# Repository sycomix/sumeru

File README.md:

# sumeru
  An open-source RISC-V CPU core and hardware platform for Altera Cyclone-IV FPGAs.

## Coremark Performance

### Summary

Sumeru @ 75 MHz - 3 stage pipeline - 4K ICACHE 4K DCACHE - MEM STACK

Compiler Flag | Binary Size | Result
------------- | ----------- | ------
-Os | 11784 | 100
-O | 13008 | 105
-O2 | 13092 | 133
-O3 | 16280 | 143

** MEM MALLOC and MEM STATIC performance is similar

### Detail

```
2K performance run parameters for coremark.
CoreMark Size    : 666
Total ticks      : 1165127873
Total time (secs): 15
Iterations/Sec   : 133
Iterations       : 2000
Compiler version : 9.2.0
Compiler flags   : -O2
Memory location  : STACK
seedcrc          : 0xe9f5
[0]crclist       : 0xe714
[0]crcmatrix     : 0x1fd7
[0]crcstate      : 0x8e3a
[0]crcfinal      : 0x4983
Correct operation validated. See README.md for run and reporting rules.

2K performance run parameters for coremark.
CoreMark Size    : 666
Total ticks      : 1165095923
Total time (secs): 15
Iterations/Sec   : 133
Iterations       : 2000
Compiler version : 9.2.0
Compiler flags   : -O2
Memory location  : BSS
seedcrc          : 0xe9f5
[0]crclist       : 0xe714
[0]crcmatrix     : 0x1fd7
[0]crcstate      : 0x8e3a
[0]crcfinal      : 0x4983
Correct operation validated. See README.md for run and reporting rules.

2K performance run parameters for coremark.
CoreMark Size    : 666
Total ticks      : 1165033531
Total time (secs): 15
Iterations/Sec   : 133
Iterations       : 2000
Compiler version : 9.2.0
Compiler flags   : -O2
Memory location  : HEAP
seedcrc          : 0xe9f5
[0]crclist       : 0xe714
[0]crcmatrix     : 0x1fd7
[0]crcstate      : 0x8e3a
[0]crcfinal      : 0x4983
Correct operation validated. See README.md for run and reporting rules.
```

## Commercial soft-core performance 

*Sumeru @ 75 MHz - 3 stage pipeline - 4K ICACHE 4K DCACHE - MEM STACK - Cyclone IV = 143 Coremark*

* [Altera NIOS II CycloneIII](https://www.eembc.org/coremark/view.php?benchmark_seq=1535)
* [Altera Nios II - 80 MHz (apple2apple 119 Coremark)](https://www.eembc.org/coremark/view.php?benchmark_seq=1336)
* [Altera Nios II - 200 MHz](https://www.eembc.org/coremark/view.php?benchmark_seq=1486)
* [Altera Nios II - 200 MHz](https://www.eembc.org/coremark/view.php?benchmark_seq=1487)
* [Altera Nios II/f - 100 MHz](https://www.eembc.org/coremark/view.php?benchmark_seq=2483)

* [Xilinx MicroBlaze v7.20.d in Spartan XC3S700A FPGA, 3-stage pipeline, 2K/2K cache](https://www.eembc.org/coremark/view.php?benchmark_seq=1042)
* [Xilinx MicroBlaze v7.20.d in Spartan XC3S700A FPGA, 5-stage pipeline, 4K/4K cache, integer divider, barrel shifter - 62.5 MHz (apple2apple 103 Coremark)](https://www.eembc.org/coremark/view.php?benchmark_seq=1043)
* [Xilinx MicroBlaze 7.10d in Virtex4-FX20 FPGA, 5-stage pipeline, 16K/16K cache](https://www.eembc.org/coremark/view.php?benchmark_seq=1287)
* [Xilinx MicroBlaze v8.20.b in Virtex5 FPGA, 5-stage pipeline, 16K/16K cache](https://www.eembc.org/coremark/view.php?benchmark_seq=1345)

[Coremark Results Website](https://www.eembc.org/coremark/scores.php)

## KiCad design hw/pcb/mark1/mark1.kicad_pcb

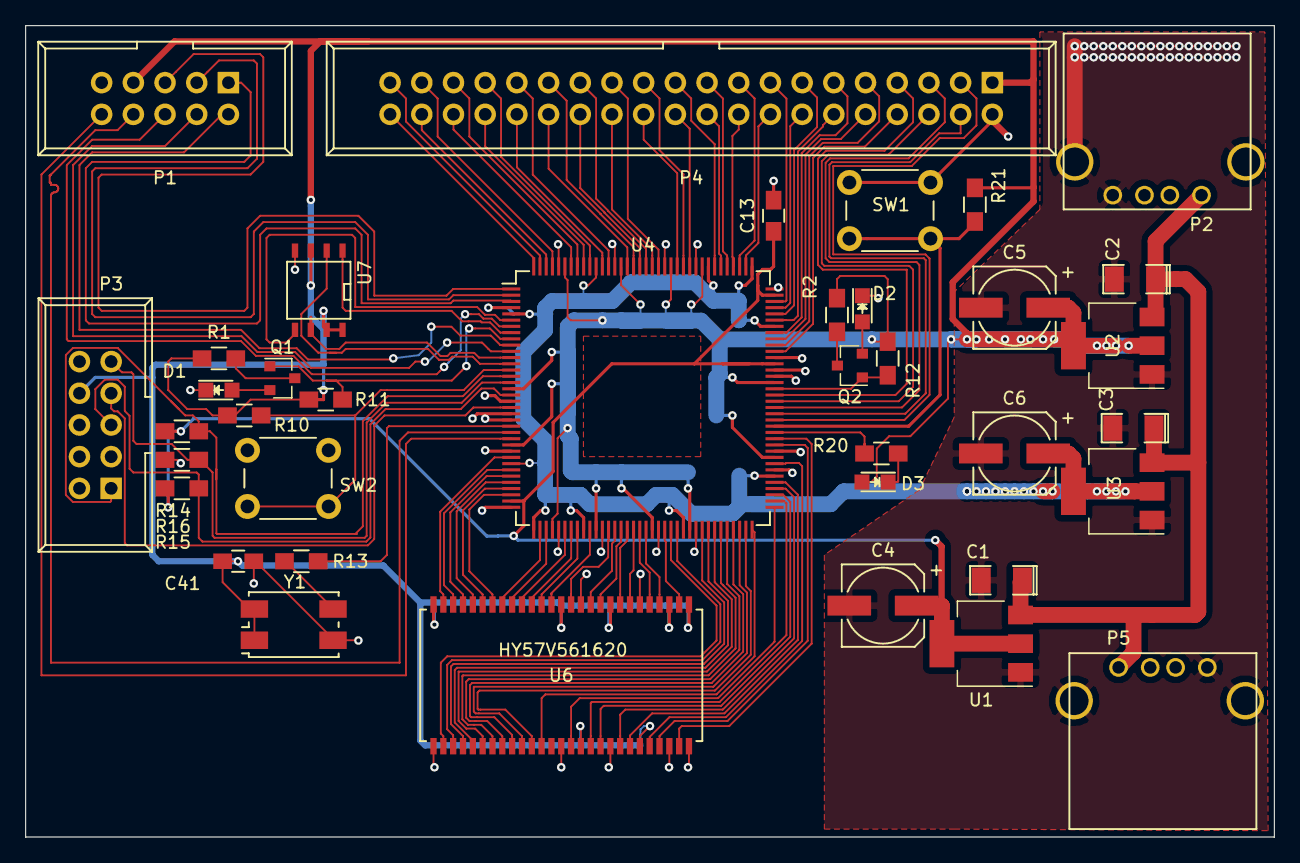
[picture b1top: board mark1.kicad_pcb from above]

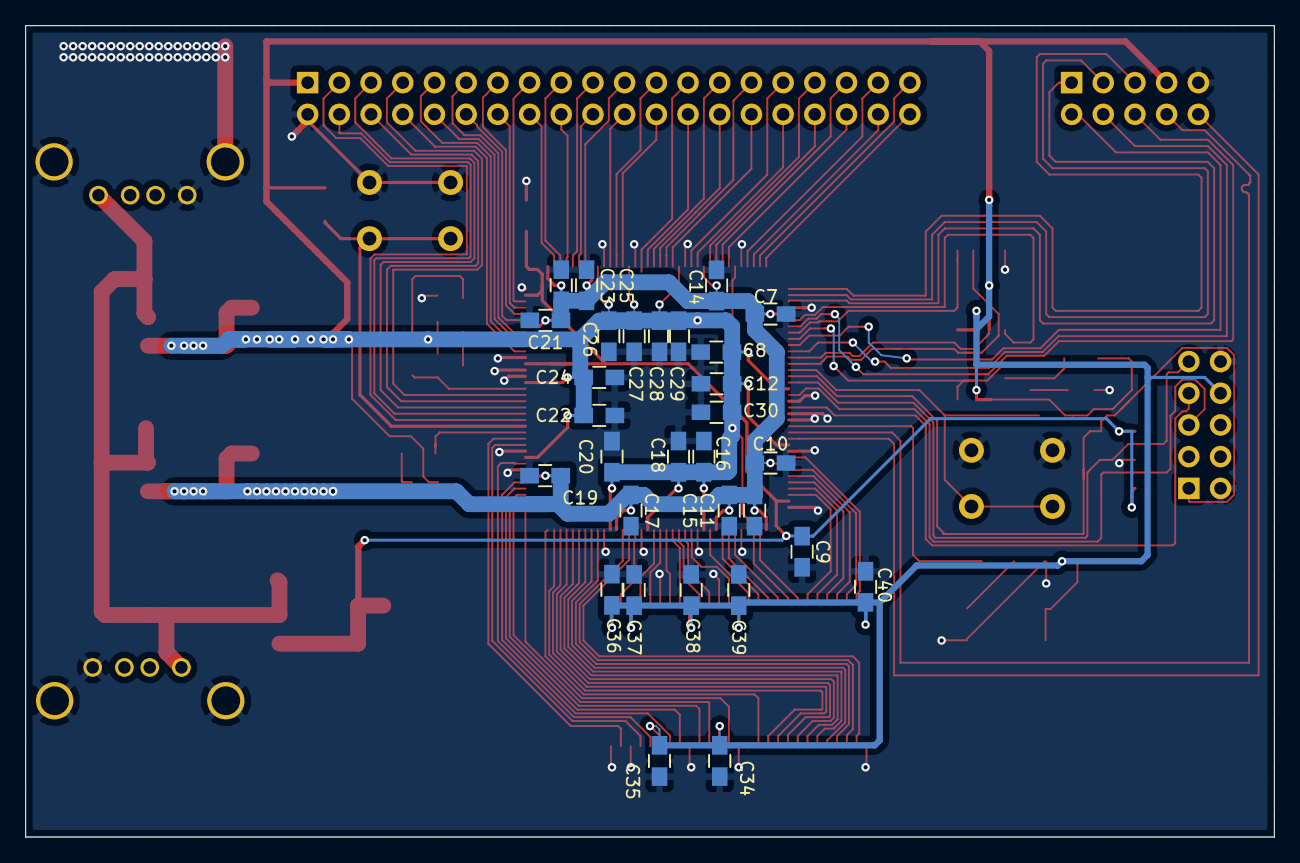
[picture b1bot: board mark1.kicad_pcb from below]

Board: 2 copper layers, 100.1 x 65.0 mm, 68 parts (30 on the bottom side), 110 nets.

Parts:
C1, C2, C3: 10uF; SMD-1206_Pol
C4, C5, C6: 100uF; c_elec_6.3x7.7
C7, C8, C9, C10, C11, C12, C13, C14, C15, C16, C17, C18, C19, C20, C21, C22, C23, C24, C25, C26, C27, C28, C29, C30, C34, C35, C36, C37, C38, C39, C40, C41: 100nF; C_0805_HandSoldering
D1, D2, D3: LED; LED_0805
P1, P3: CONN_02X05; IDC_Header_Straight_10pins
P2, P5: USB_A
P4: CONN_02X20; IDC_Header_Straight_40pins
Q1, Q2: MMBT3904; SOT-23
R1, R2, R16, R20: 1K; R_0805_HandSoldering
R10, R11, R12, R14, R15: 10K; R_0805_HandSoldering
R13: 33; R_0805_HandSoldering
R21: 1k; R_0805_HandSoldering
SW1, SW2: SW_Push; SW_PUSH_6mm_h4.3mm
U1: AMS1117-2.5; SOT-223
U2: AMS1117-3.3; SOT-223
U3: AMS1117-1.2; SOT-223
U4: EP4CE10E22C8N; TQFP-144_20x20mm_Pitch0.5mm
U6: HY57V561620; WIN_TSOP-54
U7: W25Q32FVSSIQ; SOIC-8-N
Y1: Crystal_GND23; Crystal_SMD_7050_4Pads_R

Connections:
/FPGA Configuration Circuitry/FLASH_MISO: U4.13, U7.2
/FPGA Configuration Circuitry/FLASH_MOSI: U4.6, U7.5
/FPGA Configuration Circuitry/FLASH_SCK: U4.12, U7.6
/FPGA Configuration Circuitry/FLASH_nCE: U4.8, U7.1
/FPGA Configuration Circuitry/F_CLK1: R13.2, U4.23
/FPGA Configuration Circuitry/JTAG_TCK: P3.9, R16.2, U4.16
/FPGA Configuration Circuitry/JTAG_TDI: P3.1, R14.2, U4.15
/FPGA Configuration Circuitry/JTAG_TDO: P3.7, U4.20
/FPGA Configuration Circuitry/JTAG_TMS: P3.5, R15.2, U4.18
/FPGA IO Circuitry/SDRAM1: U4.28, U6.26
/FPGA IO Circuitry/SDRAM2: U4.30, U6.25
/FPGA IO Circuitry/SDRAM3: U4.31, U6.24
/FPGA IO Circuitry/SDRAM4: U4.32, U6.23
/FPGA IO Circuitry/SDRAM5: U4.33, U6.22
/FPGA IO Circuitry/SDRAM6: U4.34, U6.21
/FPGA IO Circuitry/SDRAM7: U4.38, U6.20
/FPGA IO Circuitry/SDRAM8: U4.39, U6.19
/FPGA IO Circuitry/SDRAM9: U4.42, U6.18
/FPGA IO Circuitry/SDRAM10: U4.43, U6.17
/FPGA IO Circuitry/SDRAM11: U4.44, U6.16
/FPGA IO Circuitry/SDRAM12: U4.46, U6.15
/FPGA IO Circuitry/SDRAM13: U4.49, U6.13
/FPGA IO Circuitry/SDRAM14: U4.50, U6.11
/FPGA IO Circuitry/SDRAM15: U4.51, U6.10
/FPGA IO Circuitry/SDRAM16: U4.52, U6.8
/FPGA IO Circuitry/SDRAM17: U4.53, U6.7
/FPGA IO Circuitry/SDRAM18: U4.54, U6.5
/FPGA IO Circuitry/SDRAM19: U4.55, U6.4
/FPGA IO Circuitry/SDRAM20: U4.58, U6.2
/FPGA IO Circuitry/SDRAM21: U4.59, U6.29
/FPGA IO Circuitry/SDRAM22: U4.60, U6.30
/FPGA IO Circuitry/SDRAM23: U4.64, U6.31
/FPGA IO Circuitry/SDRAM24: U4.65, U6.32
/FPGA IO Circuitry/SDRAM25: U4.66, U6.33
/FPGA IO Circuitry/SDRAM26: U4.67, U6.34
/FPGA IO Circuitry/SDRAM27: U4.68, U6.35
/FPGA IO Circuitry/SDRAM28: U4.69, U6.36
/FPGA IO Circuitry/SDRAM29: U4.70, U6.37
/FPGA IO Circuitry/SDRAM30: U4.71, U6.38
/FPGA IO Circuitry/SDRAM31: U4.72, U6.39
/FPGA IO Circuitry/SDRAM32: U4.73, U6.42
/FPGA IO Circuitry/SDRAM33: U4.74, U6.44
/FPGA IO Circuitry/SDRAM34: U4.75, U6.45
/FPGA IO Circuitry/SDRAM35: U4.76, U6.47
/FPGA IO Circuitry/SDRAM36: U4.77, U6.48
/FPGA IO Circuitry/SDRAM37: U4.80, U6.50
/FPGA IO Circuitry/SDRAM38: U4.83, U6.51
/FPGA IO Circuitry/SDRAM39: U4.84, U6.53
F_CLK2: P1.8, U4.24
F_CLK3: P1.10, U4.25
F_CLK4: P4.7, U4.91
F_CLK5: P4.6, U4.90
F_CLK6: P4.5, U4.89
F_CLK7: P4.4, U4.88
GND: C1.2, C2.2, C3.2, C4.2, C5.2, C6.2, C7.2, C8.2, C9.2, C10.2, C11.2, C12.2, C13.2, C14.2, C15.2, C16.2, C17.2, C18.2, C19.2, C20.2, C21.2, C22.2, C23.2, C24.2, C25.2, C26.2, C27.2, C28.2, C29.2, C30.2, C34.2, C35.2, C36.2, C37.2, C38.2, C39.2, C40.2, C41.1, D1.1, D2.1, P1.9, P2.4, P2.5, P3.2, P3.10, P4.2, P5.4, P5.5, R16.1, SW1.1, SW2.1, U1.1, U2.1, U3.1, U4.4, U4.19, U4.21, U4.22, U4.27, U4.36, U4.41, U4.48, U4.57, U4.63, U4.79, U4.82, U4.94, U4.95, U4.97, U4.108, U4.118, U4.123, U4.131, U4.140, U6.6, U6.12, U6.28, U6.41, U6.46, U6.52, U6.54, U7.4, Y1.2
unnamed: D1.2, Q1.2
unnamed: D2.2, Q2.2
unnamed: D3.1, R20.2
unnamed: P1.1, U4.3
unnamed: P1.2, U4.10
unnamed: P1.3, U4.2
unnamed: P1.4, U4.11
unnamed: P1.5, U4.1
unnamed: P1.6, U4.7
unnamed: Q1.1, R11.1, U4.9
unnamed: Q1.3, R1.2
unnamed: Q2.1, R12.1, U4.92
unnamed: Q2.3, R2.2
unnamed: R10.1, SW2.2, U4.14
unnamed: R13.1, Y1.3
unnamed: R21.1, SW1.2, U4.86
PIN85: R20.1, U4.85
PIN87: P4.3, U4.87
PIN98: P4.8, U4.98
PIN99: P4.9, U4.99
PIN100: P4.10, U4.100
PIN101: P4.11, U4.101
PIN103: P4.12, U4.103
PIN104: P4.13, U4.104
PIN105: P4.14, U4.105
PIN106: P4.15, U4.106
PIN110: P4.16, U4.110
PIN111: P4.17, U4.111
PIN112: P4.18, U4.112
PIN113: P4.19, U4.113
PIN114: P4.20, U4.114
PIN115: P4.21, U4.115
PIN119: P4.22, U4.119
PIN120: P4.23, U4.120
PIN121: P4.24, U4.121
PIN124: P4.25, U4.124
PIN125: P4.26, U4.125
PIN126: P4.27, U4.126
PIN127: P4.28, U4.127
PIN128: P4.29, U4.128
PIN129: P4.30, U4.129
PIN132: P4.31, U4.132
PIN133: P4.32, U4.133
PIN135: P4.33, U4.135
PIN136: P4.34, U4.136
PIN137: P4.35, U4.137
PIN138: P4.36, U4.138
PIN141: P4.37, U4.141
PIN142: P4.38, U4.142
PIN143: P4.39, U4.143
PIN144: P4.40, U4.144
VCC: C1.1, C2.1, C3.1, P2.1, P5.1, U1.3, U2.3, U3.3
VCC1p2: C6.1, C7.1, C10.1, C11.1, C14.1, C15.1, C17.1, C19.1, C21.1, C23.1, C25.1, U3.2, U3.4, U4.5, U4.29, U4.37, U4.45, U4.61, U4.78, U4.102, U4.109, U4.116, U4.134
VCC2p5: C4.1, C9.1, C13.1, R14.1, R15.1, U1.2, U1.4, U4.35, U4.96, U4.107
VCC3p3: C5.1, C8.1, C12.1, C16.1, C18.1, C20.1, C22.1, C24.1, C26.1, C27.1, C28.1, C29.1, C30.1, C34.1, C35.1, C36.1, C37.1, C38.1, C39.1, C40.1, C41.2, D3.2, P1.7, P3.8, P4.1, R1.1, R2.1, R10.2, R11.2, R12.2, R21.2, U2.2, U2.4, U4.17, U4.26, U4.40, U4.47, U4.56, U4.62, U4.81, U4.93, U4.117, U4.122, U4.130, U4.139, U6.1, U6.3, U6.9, U6.14, U6.27, U6.43, U6.49, U7.3, U7.7, U7.8, Y1.1, Y1.4

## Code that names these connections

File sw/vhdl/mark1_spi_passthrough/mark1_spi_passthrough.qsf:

# -------------------------------------------------------------------------- #
#
# Copyright (C) 1991-2014 Altera Corporation. All rights reserved.
# Your use of Altera Corporation's design tools, logic functions 
# and other software and tools, and its AMPP partner logic 
# functions, and any output files from any of the foregoing 
# (including device programming or simulation files), and any 
# associated documentation or information are expressly subject 
# to the terms and conditions of the Altera Program License 
# Subscription Agreement, the Altera Quartus II License Agreement,
# the Altera MegaCore Function License Agreement, or other 
# applicable license agreement, including, without limitation, 
# that your use is for the sole purpose of programming logic 
# devices manufactured by Altera and sold by Altera or its 
# authorized distributors.  Please refer to the applicable 
# agreement for further details.
#
# -------------------------------------------------------------------------- #
#
# Quartus II 64-Bit
# Version 14.1.0 Build 186 12/03/2014 Patches 0.19 SJ Web Edition
# Date created = 13:06:18  July 10, 2018
#
# -------------------------------------------------------------------------- #
#
# Notes:
#
# 1) The default values for assignments are stored in the file:
#		toplevel_assignment_defaults.qdf
#    If this file doesn't exist, see file:
#		assignment_defaults.qdf
#
# 2) Altera recommends that you do not modify this file. This
#    file is updated automatically by the Quartus II software
#    and any changes you make may be lost or overwritten.
#
# -------------------------------------------------------------------------- #


set_global_assignment -name FAMILY "Cyclone IV E"
set_global_assignment -name DEVICE EP4CE10E22C8
set_global_assignment -name TOP_LEVEL_ENTITY mark1_spi_passthrough
set_global_assignment -name ORIGINAL_QUARTUS_VERSION "14.1.0 SP0.19"
set_global_assignment -name PROJECT_CREATION_TIME_DATE "13:06:18  JULY 10, 2018"
set_global_assignment -name LAST_QUARTUS_VERSION "19.1.0 Lite Edition"
set_global_assignment -name PROJECT_OUTPUT_DIRECTORY output_files
set_global_assignment -name MIN_CORE_JUNCTION_TEMP 0
set_global_assignment -name MAX_CORE_JUNCTION_TEMP 85
set_global_assignment -name DEVICE_FILTER_PACKAGE TQFP
set_global_assignment -name ERROR_CHECK_FREQUENCY_DIVISOR 1
set_global_assignment -name DEVICE_FILTER_PIN_COUNT 144
set_global_assignment -name DEVICE_FILTER_SPEED_GRADE 8
set_global_assignment -name PARTITION_NETLIST_TYPE SOURCE -section_id Top
set_global_assignment -name PARTITION_FITTER_PRESERVATION_LEVEL PLACEMENT_AND_ROUTING -section_id Top
set_global_assignment -name PARTITION_COLOR 16764057 -section_id Top
set_global_assignment -name STRATIX_DEVICE_IO_STANDARD "3.3-V LVTTL"
set_location_assignment PIN_23 -to clk_50m
set_location_assignment PIN_85 -to led
set_global_assignment -name POWER_PRESET_COOLING_SOLUTION "23 MM HEAT SINK WITH 200 LFPM AIRFLOW"
set_global_assignment -name POWER_BOARD_THERMAL_MODEL "NONE (CONSERVATIVE)"
set_global_assignment -name VHDL_FILE mark1_spi_passthrough.vhd
set_global_assignment -name VHDL_FILE pll.vhd
set_global_assignment -name ENABLE_OCT_DONE OFF
set_global_assignment -name ENABLE_CONFIGURATION_PINS OFF
set_global_assignment -name ENABLE_BOOT_SEL_PIN OFF
set_global_assignment -name USE_CONFIGURATION_DEVICE OFF
set_global_assignment -name CRC_ERROR_OPEN_DRAIN OFF
set_global_assignment -name OUTPUT_IO_TIMING_NEAR_END_VMEAS "HALF VCCIO" -rise
set_global_assignment -name OUTPUT_IO_TIMING_NEAR_END_VMEAS "HALF VCCIO" -fall
set_global_assignment -name OUTPUT_IO_TIMING_FAR_END_VMEAS "HALF SIGNAL SWING" -rise
set_global_assignment -name OUTPUT_IO_TIMING_FAR_END_VMEAS "HALF SIGNAL SWING" -fall
set_global_assignment -name RESERVE_ALL_UNUSED_PINS_WEAK_PULLUP "AS INPUT TRI-STATED"
set_global_assignment -name RESERVE_DATA0_AFTER_CONFIGURATION "USE AS REGULAR IO"
set_global_assignment -name RESERVE_DATA1_AFTER_CONFIGURATION "USE AS REGULAR IO"
set_global_assignment -name RESERVE_FLASH_NCE_AFTER_CONFIGURATION "USE AS REGULAR IO"
set_global_assignment -name RESERVE_DCLK_AFTER_CONFIGURATION "USE AS REGULAR IO"
set_global_assignment -name CYCLONEII_RESERVE_NCEO_AFTER_CONFIGURATION "USE AS PROGRAMMING PIN"
set_location_assignment PIN_13 -to flash_miso
set_location_assignment PIN_6 -to flash_mosi
set_location_assignment PIN_12 -to flash_sck
set_location_assignment PIN_8 -to flash_nce
set_location_assignment PIN_11 -to mosi
set_location_assignment PIN_7 -to miso
set_location_assignment PIN_24 -to sck
set_location_assignment PIN_10 -to nce


set_instance_assignment -name PARTITION_HIERARCHY root_partition -to | -section_id Top

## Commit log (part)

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2019-12-24 Branch working
2019-12-25 ERRATICALLY BUGGY VERSION: WIP
2019-12-26 JALR (trigger_cxfer) working
2019-12-26 WIP: Load byteena and correctly sized & signed output implemented
2019-12-26 FENCE.I is working
2019-12-26 Implement DCACHE LINE FLUSH by extending the STORE INSTRUCTION - funct3 = 011 or 111
2019-12-26 DCACHE FLUSH Example in BOOTCODE.s
2019-12-27 NEW CSR bus implementation
2019-12-27 WIP: C based boot code
2019-12-28 Bugfix: STORE immediate
2019-12-28 MULTIPLY implemented
2019-12-29 Multiply working, use regfile_wren to detect valid last writte values in iexec
2019-12-30 DIVIDE working: 4 stage pipeline - 5 cycle counter delay in iexec
2019-12-30 Adjust env.sh makefiles to avoid setting MAKEFILES in env.sh -- set in Makefile instead
2019-12-30 Rehaul BOOTCODE code build strategy, IVECTOR WIP
2019-12-30 Disable -gc-sections MK_LDFLAGS
2019-12-31 Add gtkw to examples
2019-12-31 DIVEIDE Bugfix: Increase div_ctr to 6 (was 5)
2019-12-31 INTERRUPTS WIP
2020-01-01 CSR Renumbering
2020-01-01 Add intr_controller.vhd
2020-01-01 BUGFIX: Interrupt Handling in idecode
2020-01-01 **RADICAL changes to ifetch and idecode to facilitate raising of interrupts. c6ab235fc192d14625a0c713357f9949c8f2c8c9 is a know good state before these changes
2020-01-02 CSR sel bit delay introduced, INTR RETURN WIP
2020-01-03 CPU IDECODE Overhauld / Rewrite
2020-01-03 CPU IDECODE Overhaul / Rewrite: WIP
2020-01-03 GOOD VERSION: INTR RETURN WORKING. Bug: Don't set cxfer on OP_TYPE_B in decode. Bug: Output complete address from interrupt handler instead of a partial vector; Partial vector with concatenation does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
2020-01-04 Revert last changes to CSR numbering
2020-01-04 Buggy Version. Seem like previous fix to intr_handler to emit full address still does not work. This version shows different behaviour for simulation and actual. Seems like immediate is not getting c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
2020-01-04 Rearrange assignment for iexec_in.imm <= ctx_pc_switch
2020-01-04 IRET (aka. switch) seems to be working -- more testing needed
2020-01-05 WIP: Getting Ready to RUN riscv-tests
2020-01-05 Add riscv-test to REPO
2020-01-05 Adjust riscv-tests for SAKE
2020-01-05 Makefile changed to run risc-test via BC_FILE variable
2020-01-05 SHIFT BUGFIX - srai sign bit fix
2020-01-05 riscv-test env add support for test data
2020-01-05 ***GOOD VERSION: All riscv rv32i tests except fence.i, mul and div are tested working
2020-01-05 Bug fix: mulh was being decoded as shift -- mulh working
2020-01-05 DIV(U) and REM(U) working with minimal latency (emphirically checked @85MHZ) of pipeline 8 and counter 9 -- counter 8 does not work nor does pipeline 6
2020-01-05 Modify riscv-test fence test to perform a D-Cache line flush prior to initiating the fence.i instruction
2020-01-05 **GOOD VERSION: All riscv rv32imu tests pass with this version -- time to reintegrate back from REWORK into cpu_v2 master
2020-01-06 Reintroduce intr_controller, csr_timer, csr_counters. Renumber CSR Registers to coform to RV spec
2020-01-06 ***GOOD VERSION: RV32IMU-tested+intr: INTR RET is working
2020-01-06 Minimum delay requied between writing to CSR_REG_PC_SWITCH and CSR_REG_SWITCH is 2 NOPS
2020-01-06 Add support for interrupt reset
2020-01-06 INTR ret wip
2020-01-06 cometic change reverted idecode
2020-01-06 **GOOD VERSION: INTERRUPT HANDLING IS DONE : Invariant If device intr-ack csr is written just before csr_switch is written the device intr-line is being lowered in time to avoid errors.
2020-01-06 REWORK : CPU_V2 : RV32IMU - riscv-test PASS : Re-integrated back into master sumeru/cpu : with history commits from REWORK branch
2020-01-06 Adjust jtag .sof path, remove obsolete examples, remove PENDING dir
2020-01-08 mark1_spi_passthrough: remove pll.qip
2020-01-08 mark1_spi_passthrough
2020-01-08 Import RPI spi-flash programs (scheme)
2020-01-08 Reset (aclr) cycle/inst counters on boot
2020-01-08 SIO: impl started
2020-01-09 UART Transmit working at 115200
2020-01-09 asm_handle_interrupt and handle_interrupt -- register saving interrupt handling code -- caveat we save/restore 15 registers (60 bytes) -- need a better strategy
2020-01-10 uart: cosmetic changes
2020-01-10 UART RECV WIP
2020-01-10 UART RX Impl done
2020-01-10 UART RECV working -- decent performance -- few errors at full speed back to back echo recv->txmit
2020-01-12 Add compile/*.log to .gitignore file
2020-01-13 BUGFIX: entry.s sp error
2020-01-13 boot.c: timer+shiftblink code
2020-01-14 Remove UART Clk
2020-01-14 UART renovation WIP
2020-01-14 boot.c: Introduce Acknowledge Uart TX intr sematics
2020-01-14 New TX Working
2020-01-15 NEW TX Code -- stable and performs without errors
2020-01-16 SIO REWORK2 uart stuff removed, impl restarted
2020-01-16 Remove C1 clk from pll
2020-01-17 Timer: remove intr_enabled sematics
2020-01-17 Introduce pdma for uart
2020-01-17 Timer: 0x4000F - working with TX 0x10
2020-01-17 Remove debugging signals
2020-01-17 Move to Quartus 18.1 -- fixes blink+tx bugs
2020-01-17 Timer: 0x4F - working with TX 0x10 - Quartus 18.1
2020-01-19 ALL WORKING Revision at 80:MHz -- Special fix: csr_reg is set to zero on each cycle in cpu_exec
2020-01-19 ***GOLD: TIMER+TX+RX+SHIFTBLINK ALL WORKING at 80MHz
2020-01-20 Add periph_dma.vhd
2020-01-20 New C Bootcode WIP
2020-01-22 Bootloader WIP
2020-01-23 BOOTLOADER WIP: change uart rx and tx buffer location to 0x2000 and 0x2100
2020-01-23 BOOTLOADER CLIENT: tools/bootloader_client.c: WIP
2020-01-23 Move machine includes to sw/includes
2020-01-23 KERNEL WORKING with Quartus 19.1 [timing/wierd store-word error with 14.1]
2020-01-23 bootloader_client : write data upto 32 byte boundaries, padding with zero as necessary
2020-01-24 Rename bootloader_client to bootloader_uart_client and check in compiled binary
2020-01-24 Rehaul scripts and quartus build infra
2020-01-24 sw/include/machine/memctl.h
2020-01-25 CPU: Introduce IVECTOR_ADDR -- csr_misc
2020-01-25 Blinky TX w/ Shift Blink working
2020-01-25 Re-import bluetooth_le_terminal code
2020-01-26 Add COUNTERS ENABLE code to Attic
2020-01-26 **Improve: Set csr_sel_reg and csr_sel_op early in cpu_stage_iexec
2020-01-26 add ATTIC/CSR_ALLINCOUNTERS.diff
2020-01-26 add rdtime() rdinstret() to csr.h
2020-01-26 add likely unlikely macro definitions to blinky/boot.c as an exmple
2020-01-27 bluetooth loader WIP
2020-01-27 post.mk: when generating kernel binaries add a 16 byte zero padding to aid with flush in bootloader fimrware
2020-01-27 **bluetooth_bootloader_client working
2020-01-27 Add cpu/RBF/mark1_spi_passthrough.rbf
2020-01-27 bluetooth_bootloader_client: improve status messages
2020-01-27 Remove old tools: genloadableimage, uartcodedump and uartcodeloader
2020-01-27 Add binaries for bluetooth_bootloader_client & contrib/pygattlib/src/libgatt.so
2020-01-27 add bluetooth_bootloader_client -- was missing from previous commits
2020-01-27 commit missing bluetooth_bootloader support files
2020-01-27 bluetooth_bootloader_client
2020-01-27 SCRATCH: A LIBC based kernel w/ entry.S (crt0.s)
2020-01-27 Remove i386 optimisations from libc
2020-01-27 **SCRATCH LIBC KERNEL Printf working
2020-01-29 Lower SYSCLOCK to 75@MHZ
2020-01-29 ATTIC/CAUSES_HANG.diff
2020-01-29 Kernel Scratch working iwth uart0_blocking write -- todo next printf
2020-01-29 Add load and terminal targets to kernels/*/Makefile
2020-01-30 Move back to Quartus 14.1 @ 75 MHz -- tested, it works
2020-01-30 Set Quartus Optimization Mode to AGGRESSIVE PERFORMANCE, without it kernels/scratch does not printf ??, HK what is going on :
2020-02-03 Add intergers parameters to scratch.c printf code
2020-02-03 **** CPU+Dhrystone working at 75MHz -- Result 30.65 DMIPS
2020-02-03 **BUG : Fix flushing of buffers in boot.c. ***Move to 16 byte bootclient protocol
2020-02-03 ***Move to 16 byte bootclient protocol : bootloader_uart_client.c
2020-02-03 Add optimized versions of strcmp strlen strcpy
2020-02-03 Dummy commit : Seems like this version actually achives 31.80 DMIPS - Takes 67100013 cycles at 75MHz for 50000 Dhrystone 2.2
2020-02-04 Revert LIBC strcmp strcpy and strlen optimizations as a bug was discovered in strcpy and/or strcmp
2020-02-04 Move common uart0 code to sys-libs/driers
2020-02-04 Symlink uart0 driver in cpu/BOOT
2020-02-04 UART Code reorganization WIP
2020-02-04 blinky: Adjust makefile for common uart code
2020-02-04 UART common code factorisation WIP
2020-02-04 Introduce uart_io.[ch] in libc
2020-02-04 COREMARK Benchmark -- result ~100 (Iterations per second) over 5000 iterations
2020-02-05 Remove mistakenly commited vim swapfile in kernel/scratch dir
2020-02-05 kernels entry.S set stack to memory top ... DEFAULT_STACK_START_LOC 0x1FFFFF0
2020-02-05 Add support for MEM_METHOD malloc to coremark, switch benchmark to use MALLOC by default
2020-02-10 Start development of Scheme intepreter
2020-02-10 K2 scheme intepreter development started
2020-02-12 UART -- Add support for configurable BAUD rates
2020-02-12 wip: scheme/scheme.c
2020-02-12 Make cpu/BOOTCODE uart functions independent as we move kernels to use a new uart strategy (2buf)
2020-02-13 cpu/BOOTCODE changes: simplification
2020-02-13 UART: Do not reset curpos when BIT(31) of CTRL register is set -- required to facilitate of reading rx/tx ctrl registers during rx/tx operation
2020-02-16 WIP -- non functional commit, i.e. bug still reproduces -- comment out lines in handle_interrupt
2020-02-16 ***BUG FILE: icache readcache was not invalidating cache lines correctly on flush - fixed
2020-02-16 BOOTCODE: set led to known state (on) on Jmp to loaded code
2020-02-16 newk: add experiment
2020-02-17 **BUGFIX : CPU STAGE IEXEC, STORE DATA WAS NOT BEING SET CORRECTLY, CAUSE WRONG DATA TO BE WRITTEN ON STORES -- FIXED
2020-02-17 NEW RX TX INTRHANDLING work restarted WIP
2020-02-17 csr.h remove extra init code from uart0_get_tx/rx
2020-02-17 Add note on GCC volatile code generation bug to ATTIC/GCC-VOLATILE-bug.txt
2020-02-18 uart0.h WIP
2020-02-18 ***BUG FIX: csr_uart in rx section, when idle and reset_curpos is set reset rx_buf_curpos otherwise gpio_get_rx will keep returning the last value istead of 0
2020-02-18 driver/interrupts.c: WIP
2020-02-18 Add RBF File for SUMERU_RV32IMU_V2020R1b7
2020-02-18 entry.S re-enable mallock pool population
2020-02-18 tools/RPI: Commit RPI tools
2020-02-18 newk.c: use fgets fputs
2020-02-18 dhrystone/Makefile : adjust ticks to 75MHz
2020-02-18 BUG FIX entry.S -- asm_handle_interrupt was setting sp to 0x2000 instead of servicing interrupts on the user stack
2020-02-19 Coremark : Reset code to coremark-master repo -- no changes in base code. Changes are limited to core_portme.[ch]
2020-02-19 newk example use malloc for buffer
2020-02-19 Bluetooth tools: Make MAC address and Write Handle address configurable via the command line
2020-02-19 REAME markdown
2020-02-19 README markdown
2020-02-20 LIBC: Add optimized routines for memcpy,memcmove,strcpy,strlen,memset,strcmp
2020-02-20 re-haul sw/kernels/*/Makefile to use bluetooth.cfg, enable gc-sections, use -O2 instead of -Os
2020-02-20 bluetooth: cfg change
2020-02-21 ** NEW UART code - Both TX and RX are streambuf based
2020-02-22 NEW UART code WIP
2020-02-23 cpu/ATTIC/4K-ROM.diff
2020-02-23 Bugwork WIP
2020-02-23 ATTIC/2K-BootAt0x10000.diff ATTIC/72MHz-clk.diff
2020-02-23 NEWK STREAMBUF Code working with uart_blocking_read/write echo length = 1
2020-02-23 .gitignore entires
2020-02-23 COREMARK: Call uart0_start_engine in core_portme.c
2020-02-23 Move sw/kernels/newk to sw/kernels/scratch
2020-02-24 scratch WIP
2020-02-24 New Consprod WIP
2020-02-26 Conprod bugfix
2020-03-02 sumeru constants: add commented settings for 72MHz UART counters
2020-03-04 ATTIC/PulseView.conf
2020-03-04 Add new kernel to aid in bug search : sw/kernels/bugfind
2020-03-05 SUMERU_RV32IMU_V2020R1b8
2020-03-06 CONSPROD RECV WIP
2020-03-11 Add ILI9488 (320x480) LCD Driver datasheet
